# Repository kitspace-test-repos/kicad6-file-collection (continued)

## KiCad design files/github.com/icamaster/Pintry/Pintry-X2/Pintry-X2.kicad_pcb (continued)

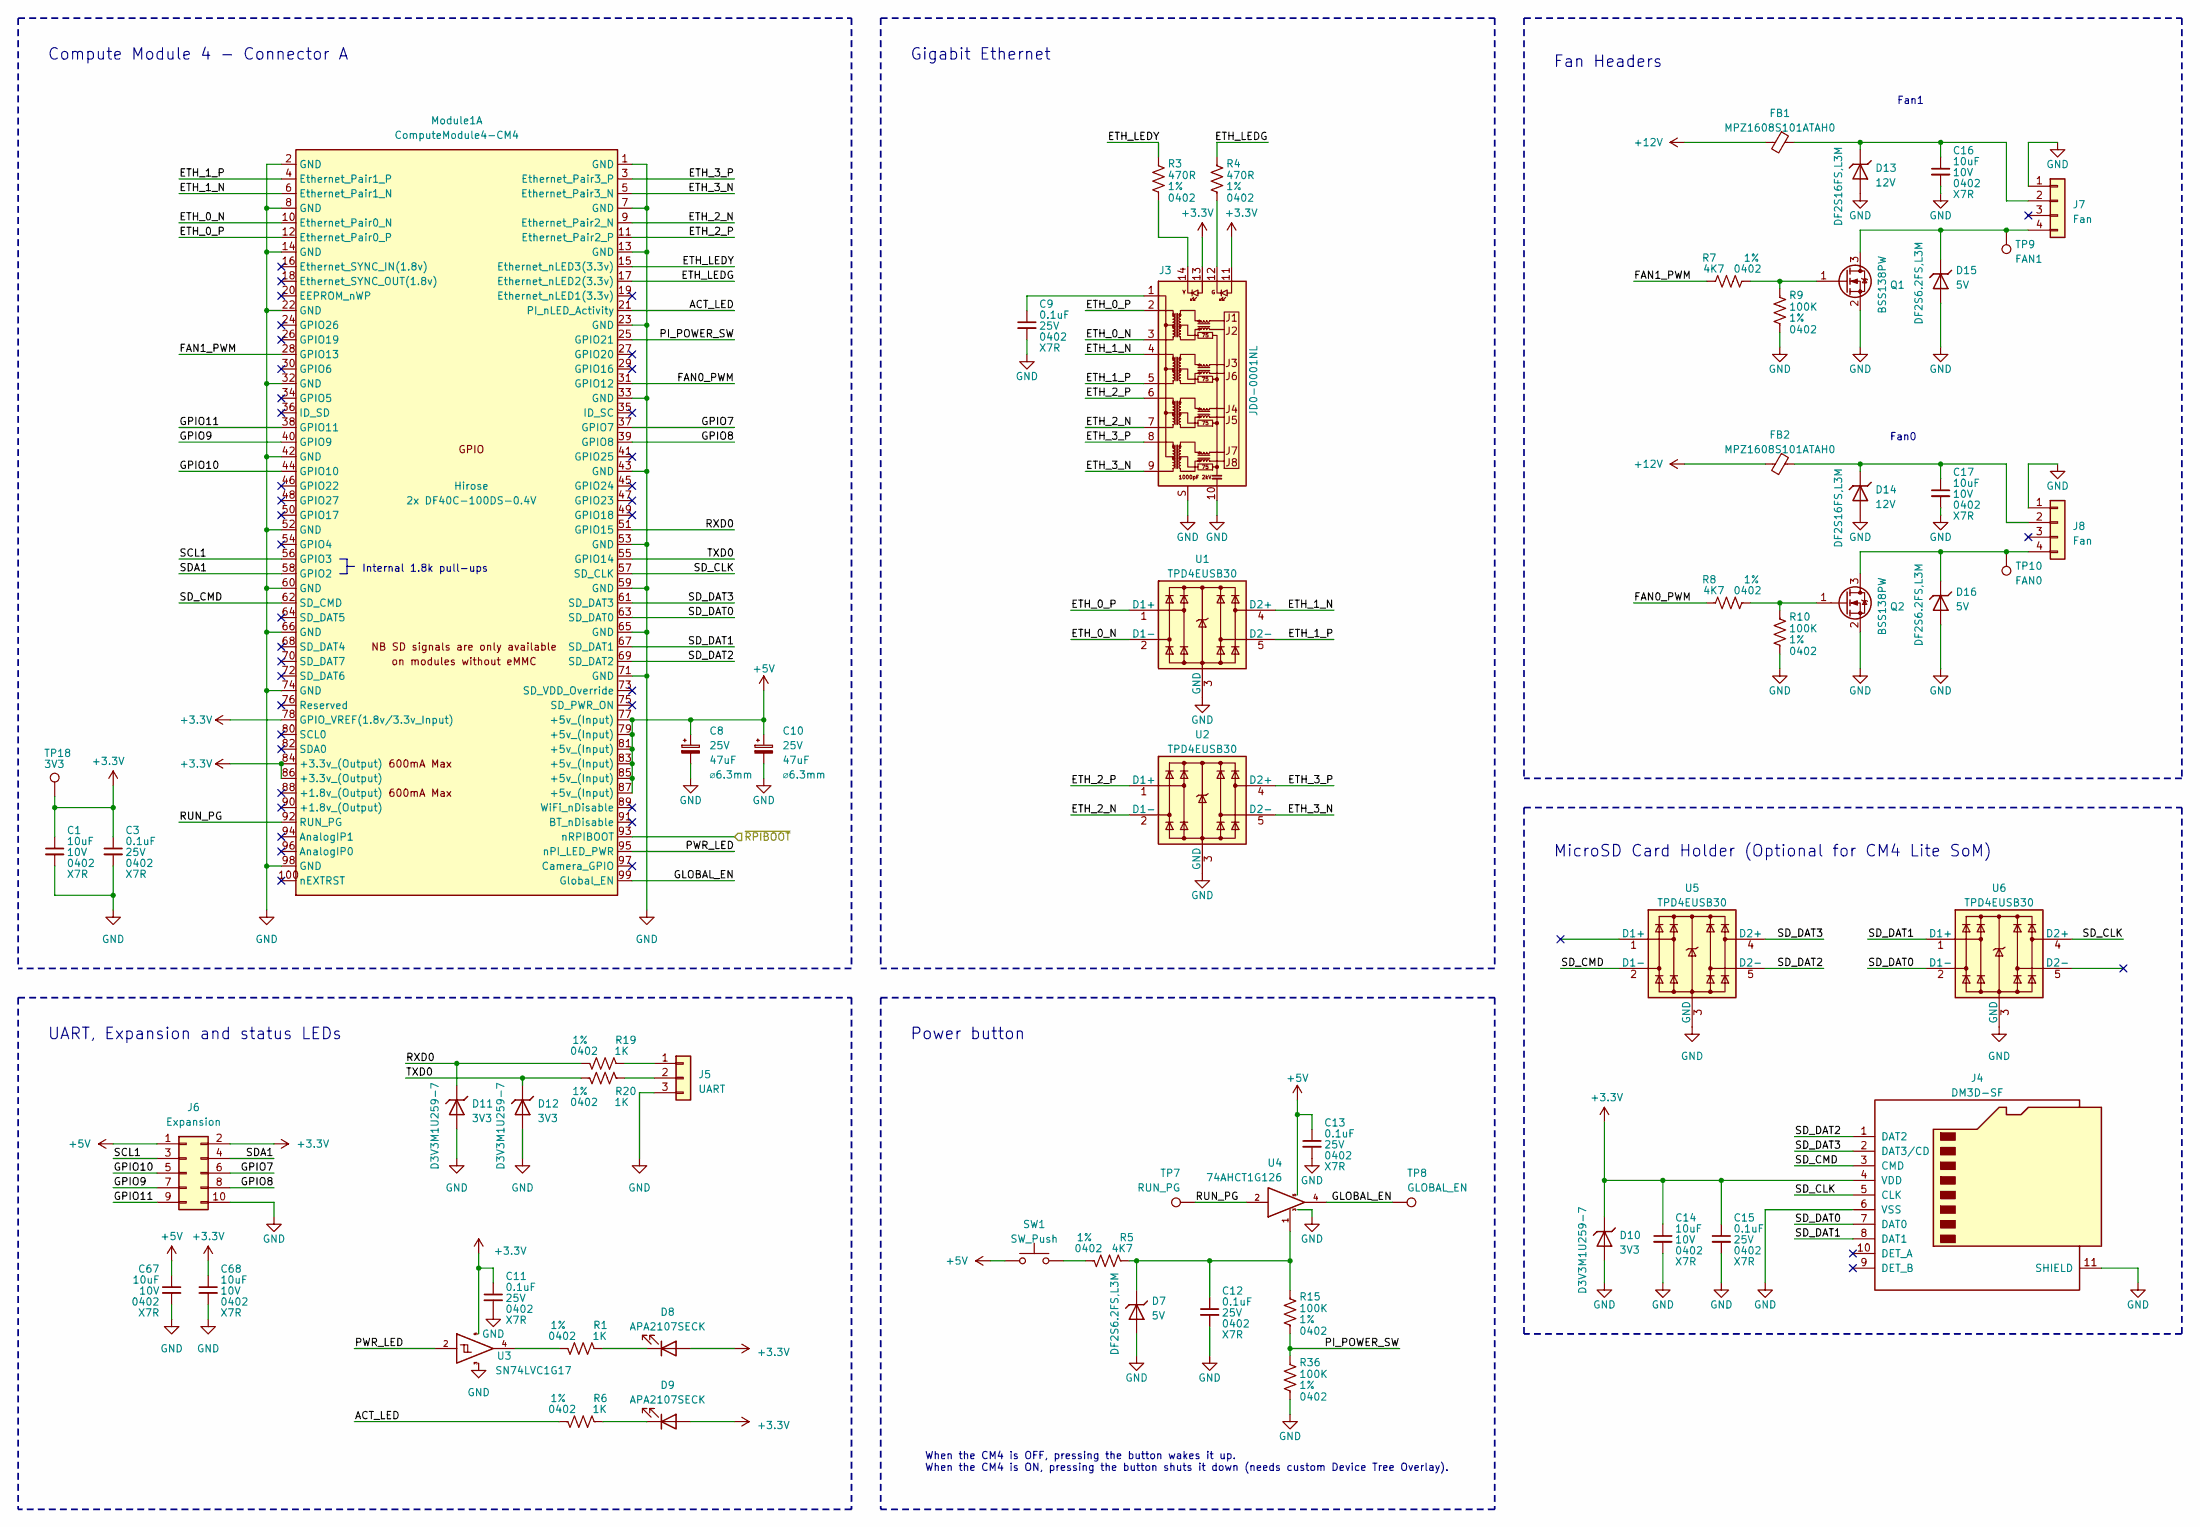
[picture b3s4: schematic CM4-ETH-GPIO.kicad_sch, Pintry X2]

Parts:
C1, C14, C16, C17, C67, C68: 10uF; C_0402_1005Metric; Voltage Rating 10V
C3, C9, C11, C12, C13, C15: 0.1uF; C_0402_1005Metric; Voltage Rating 25V
C8, C10: 865080443007; CP_Elec_6.3x5.4; Voltage 25V; Part Number 865080443007
D7, D15, D16: DF2S6.2FS,L3M; D_SOD-923; Part Number DF2S6.2FS,L3M
D8, D9: APA2107SECK; PartNumber APA2107SECK/J4-PRV
D10, D11, D12: D3V3M1U259-7; D_SOD-923; Part Number D3V3M1U2S9-7
D13, D14: DF2S16FS,L3M; D_SOD-923; Part Number DF2S16FS,L3M
FB1, FB2: MPZ1608S101ATAH0; L_0603_1608Metric; Part Number MPZ1608S101ATAH0
J3: JD0-0001NL; Pulse-JD0-0001NL-0-0-MFG; Part Number JD0-0001NL
J4: DM3D-SF; microSD_HC_Hirose_DM3D-SF; Part Number DM3D-SF
J5: UART; PinHeader_1x03_P2.54mm_Vertical; Part Number PH1-03-UA
J6: Expansion; PinHeader_2x05_P2.54mm_Vertical; Part Number 2PH2-10-UA
J7, J8: Fan; Molex_KK-254_AE-6410-04A_1x04_P2.54mm_Vertical; Part Number 47053-1000
Module1: ComputeModule4-CM4; Raspberry-Pi-4-Compute-Module; Part Number 2x DF40C-100DS-0.4V
Q1, Q2: BSS138PW; SOT-323_SC-70; Part Number BSS138PW,115
R1, R6, R19, R20: 1K; R_0402_1005Metric; Tolerance 1%
R3, R4: 470R; R_0402_1005Metric; Tolerance 1%
R5, R7, R8: 4K7; R_0402_1005Metric; Tolerance 1%
R9, R10, R15, R36: 100K; R_0402_1005Metric; Tolerance 1%
SW1: SW_Push; SW_Tactile_SPST_Angled_PTS645Vx58-2LFS; Part Number 1-1825027-4
TP7: RUN_PG; TestPoint_Pad_D1.0mm
TP8: GLOBAL_EN; TestPoint_Pad_D1.0mm
TP9: FAN1; TestPoint_Pad_D1.0mm
TP10: FAN0; TestPoint_Pad_D1.0mm
TP18: 3V3; TestPoint_Pad_D1.0mm
U1, U2, U5, U6: TPD4EUSB30; USON-10_2.5x1.0mm_P0.5mm; Part Number TPD4EUSB30DQAR
U3: SN74LVC1G17; SOT-23-5; Part Number SN74LVC1G17DBVR
U4: 74AHCT1G126; SOT-353_SC-70-5; Part Number 74AHCT1G126SE-7

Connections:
+3V3: C1.1, C3.1, C11.1, C14.1, C15.1, C68.1, D8.2 (A), D9.2 (A), D10.1 (K), J3.11, J3.13, J4.4 (VDD), J6.2, Module1.78 (GPIO_VREF(1.8v/3.3v_Input)), Module1.84 (+3.3v_(Output)), Module1.86 (+3.3v_(Output)), TP18.1, U3.5 (VCC); also elsewhere on the board
+5V: C8.1, C10.1, C13.1, C67.1, J6.1, Module1.77 (+5v_(Input)), Module1.79 (+5v_(Input)), Module1.81 (+5v_(Input)), Module1.83 (+5v_(Input)), Module1.85 (+5v_(Input)), Module1.87 (+5v_(Input)), SW1.1, U4.5 (VCC); also elsewhere on the board
+12V: FB1.2, FB2.2; also elsewhere on the board
/CM4-ETH-GPIO/ACT_LED: Module1.21 (PI_nLED_Activity), R6.2
/CM4-ETH-GPIO/ETH_0_N: J3.3, Module1.10 (Ethernet_Pair0_N), U1.2 (D1-), U1.9
/CM4-ETH-GPIO/ETH_0_P: J3.2, Module1.12 (Ethernet_Pair0_P), U1.1 (D1+), U1.10
/CM4-ETH-GPIO/ETH_1_N: J3.4, Module1.6 (Ethernet_Pair1_N), U1.4 (D2+), U1.7
/CM4-ETH-GPIO/ETH_1_P: J3.5, Module1.4 (Ethernet_Pair1_P), U1.5 (D2-), U1.6
/CM4-ETH-GPIO/ETH_2_N: J3.7, Module1.9 (Ethernet_Pair2_N), U2.2 (D1-), U2.9
/CM4-ETH-GPIO/ETH_2_P: J3.6, Module1.11 (Ethernet_Pair2_P), U2.1 (D1+), U2.10
/CM4-ETH-GPIO/ETH_3_N: J3.9, Module1.5 (Ethernet_Pair3_N), U2.5 (D2-), U2.6
/CM4-ETH-GPIO/ETH_3_P: J3.8, Module1.3 (Ethernet_Pair3_P), U2.4 (D2+), U2.7
/CM4-ETH-GPIO/ETH_LEDG: Module1.17 (Ethernet_nLED2(3.3v)), R4.1
/CM4-ETH-GPIO/ETH_LEDY: Module1.15 (Ethernet_nLED3(3.3v)), R3.1
/CM4-ETH-GPIO/FAN0_PWM: Module1.31 (GPIO12), R8.1
/CM4-ETH-GPIO/FAN1_PWM: Module1.28 (GPIO13), R7.1
/CM4-ETH-GPIO/GLOBAL_EN: Module1.99 (Global_EN), TP8.1, U4.4
/CM4-ETH-GPIO/GPIO7: J6.6, Module1.37 (GPIO7)
/CM4-ETH-GPIO/GPIO8: J6.8, Module1.39 (GPIO8)
/CM4-ETH-GPIO/GPIO9: J6.7, Module1.40 (GPIO9)
/CM4-ETH-GPIO/GPIO10: J6.5, Module1.44 (GPIO10)
/CM4-ETH-GPIO/GPIO11: J6.9, Module1.38 (GPIO11)
/CM4-ETH-GPIO/PI_POWER_SW: Module1.25 (GPIO21), R15.2, R36.1
/CM4-ETH-GPIO/PWR_LED: Module1.95 (nPI_LED_PWR), U3.2
/CM4-ETH-GPIO/RUN_PG: Module1.92 (RUN_PG), TP7.1, U4.2
/CM4-ETH-GPIO/RXD0: D11.1 (K), Module1.51 (GPIO15), R19.2
/CM4-ETH-GPIO/SCL1: J6.3, Module1.56 (GPIO3)
/CM4-ETH-GPIO/SDA1: J6.4, Module1.58 (GPIO2)
/CM4-ETH-GPIO/SD_CLK: J4.5 (CLK), Module1.57 (SD_CLK), U6.4 (D2+), U6.7
/CM4-ETH-GPIO/SD_CMD: J4.3 (CMD), Module1.62 (SD_CMD), U5.2 (D1-), U5.9
/CM4-ETH-GPIO/SD_DAT0: J4.7 (DAT0), Module1.63 (SD_DAT0), U6.2 (D1-), U6.9
/CM4-ETH-GPIO/SD_DAT1: J4.8 (DAT1), Module1.67 (SD_DAT1), U6.1 (D1+), U6.10
/CM4-ETH-GPIO/SD_DAT2: J4.1 (DAT2), Module1.69 (SD_DAT2), U5.5 (D2-), U5.6
/CM4-ETH-GPIO/SD_DAT3: J4.2 (DAT3/CD), Module1.61 (SD_DAT3), U5.4 (D2+), U5.7
/CM4-ETH-GPIO/TXD0: D12.1 (K), Module1.55 (GPIO14), R20.2
/CM4-ETH-GPIO/~RPIBOOT: Module1.93 (nRPIBOOT); also elsewhere on the board
GND: C1.2, C3.2, C8.2, C9.2, C10.2, C11.2, C12.2, C13.2, C14.2, C15.2, C16.2, C17.2, C67.2, C68.2, D7.2 (A), D10.2 (A), D11.2 (A), D12.2 (A), D13.2 (A), D14.2 (A), D15.2 (A), D16.2 (A), J3.10, J3.S, J4.6 (VSS), J4.11 (SHIELD), J5.3, J6.10, J7.1, J8.1, Module1.1 (GND), Module1.2 (GND), Module1.7 (GND), Module1.8 (GND), Module1.13 (GND), Module1.14 (GND), Module1.22 (GND), Module1.23 (GND), Module1.32 (GND), Module1.33 (GND), Module1.42 (GND), Module1.43 (GND), Module1.52 (GND), Module1.53 (GND), Module1.59 (GND), Module1.60 (GND), Module1.65 (GND), Module1.66 (GND), Module1.71 (GND), Module1.74 (GND), Module1.98 (GND), Q1.2 (S), Q2.2 (S), R9.2, R10.2, R36.2, U1.3 (GND), U1.8 (GND), U2.3 (GND), U2.8 (GND), U3.3 (GND), U4.3 (GND), U5.3 (GND), U5.8 (GND), U6.3 (GND), U6.8 (GND); also elsewhere on the board
unnamed: C9.1, J3.1
unnamed: C12.1, D7.1 (K), R5.1, R15.1, U4.1
unnamed: C16.1, D13.1 (K), FB1.1, J7.2
unnamed: C17.1, D14.1 (K), FB2.1, J8.2
unnamed: D8.1 (K), R1.1
unnamed: D9.1 (K), R6.1
unnamed: D15.1 (K), J7.4, Q1.3 (D), TP9.1
unnamed: D16.1 (K), J8.4, Q2.3 (D), TP10.1
unnamed: J3.12, R4.2
unnamed: J3.14, R3.2
unnamed: J5.1, R19.1
unnamed: J5.2, R20.1
unnamed: Q1.1 (G), R7.2, R9.1
unnamed: Q2.1 (G), R8.2, R10.1
unnamed: R1.2, U3.4
unnamed: R5.2, SW1.2

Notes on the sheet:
Gigabit Ethernet
Internal 1.8k pull-ups
When the CM4 is OFF, pressing the button wakes it up. When the CM4 is ON, pressing the button shuts it down (needs custom Device Tree Overlay).
UART, Expansion and status LEDs
MicroSD Card Holder (Optional for CM4 Lite SoM)
Fan1
Fan0
Fan Headers
Power button
Compute Module 4 - Connector A

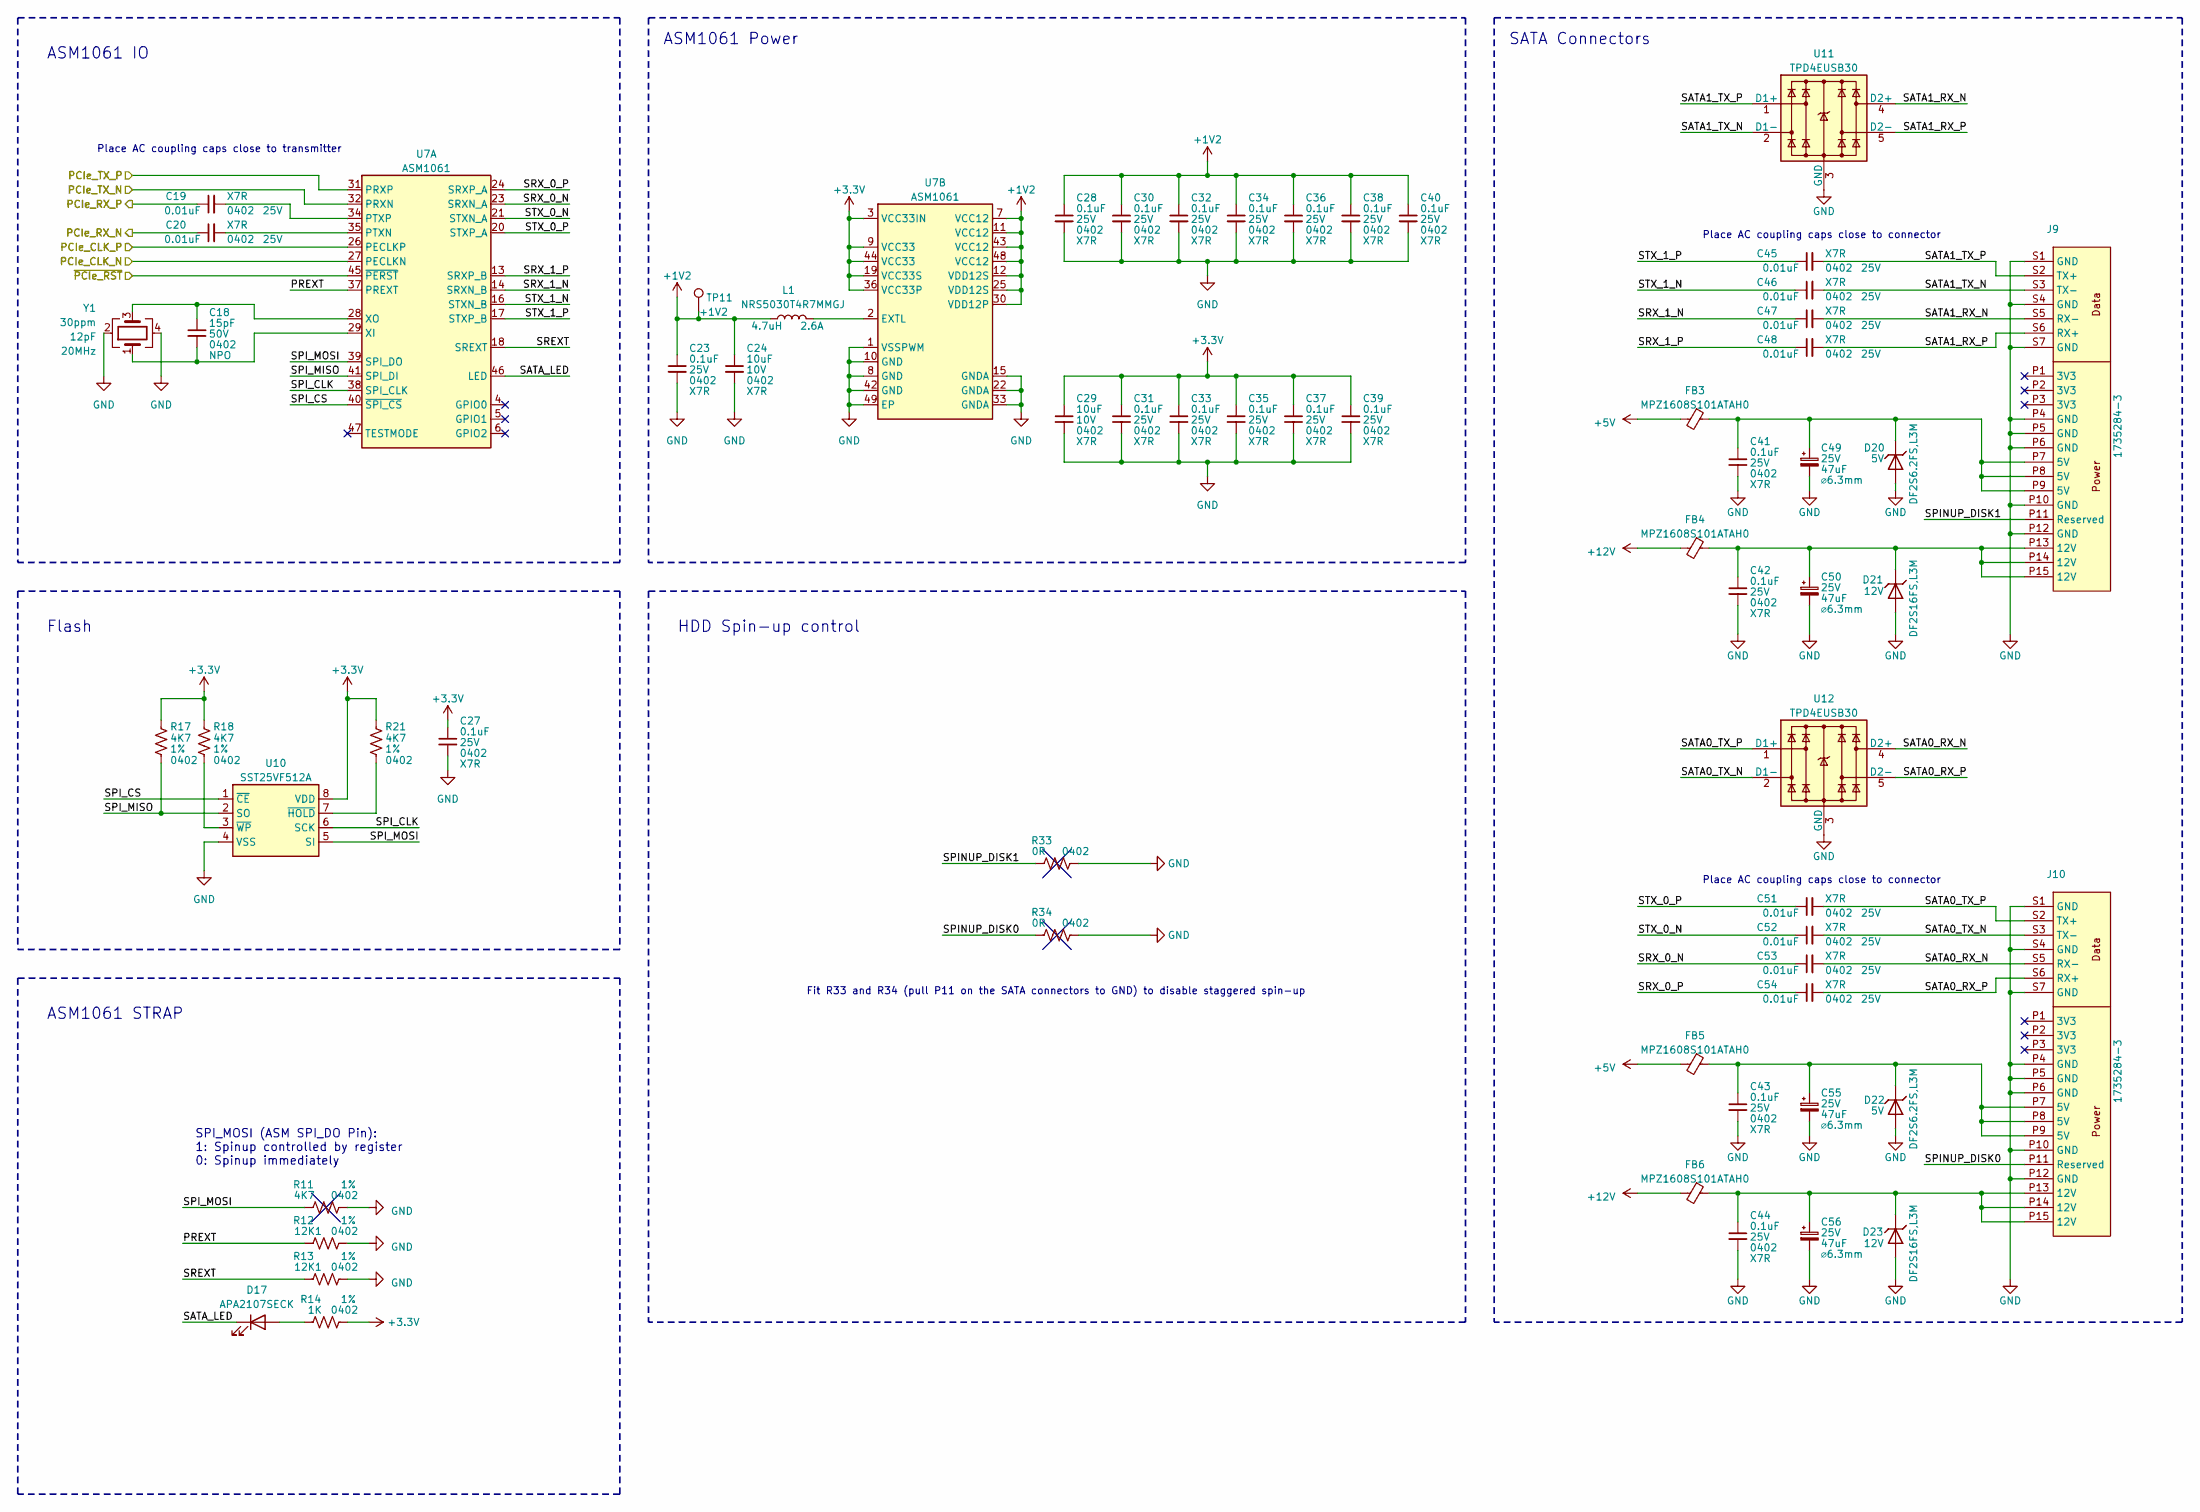
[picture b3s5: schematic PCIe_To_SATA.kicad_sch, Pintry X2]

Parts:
C18: 15pF; C_0402_1005Metric; Voltage Rating 50V
C19, C20, C45, C46, C47, C48, C51, C52, C53, C54: 0.01uF; C_0402_1005Metric; Voltage Rating 25V
C23, C27, C28, C30, C31, C32, C33, C34, C35, C36, C37, C38, C39, C40, C41, C42, C43, C44: 0.1uF; C_0402_1005Metric; Voltage Rating 25V
C24, C29: 10uF; C_0402_1005Metric; Voltage Rating 10V
C49, C50, C55, C56: 865080443007; CP_Elec_6.3x5.4; Voltage 25V; Part Number 865080443007
D17: APA2107SECK; PartNumber APA2107SECK/J4-PRV
D20, D22: DF2S6.2FS,L3M; D_SOD-923; Part Number DF2S6.2FS,L3M
D21, D23: DF2S16FS,L3M; D_SOD-923; Part Number DF2S16FS,L3M
FB3, FB4, FB5, FB6: MPZ1608S101ATAH0; L_0603_1608Metric; Part Number MPZ1608S101ATAH0
J9, J10: 1735284-3; TE_1735284-3; Part Number 1735284-3
L1: NRS5030T4R7MMGJ; L_Taiyo-Yuden_NR-50xx; Current Rating 2.6A; Part Number NRS5030T4R7MMGJ
R11, R17, R18, R21: 4K7; R_0402_1005Metric; Tolerance 1%
R12, R13: 12K1; R_0402_1005Metric; Tolerance 1%
R14: 1K; R_0402_1005Metric; Tolerance 1%
R33, R34: 0R; R_0402_1005Metric; Tolerance 1%
TP11: +1V2; TestPoint_Pad_D1.0mm
U7: ASM1061; QFN-48-1EP_7x7mm_P0.5mm_EP4.025x4.025mm
U10: SST25VF512A; SOIC-8_3.9x4.9mm_P1.27mm; Part Number SST25VF512A-33-4I-SAE-T
U11, U12: TPD4EUSB30; USON-10_2.5x1.0mm_P0.5mm; Part Number TPD4EUSB30DQAR
Y1: ECS-200-12-33-AGN-TR; Crystal_SMD_3225-4Pin_3.2x2.5mm; Part Number ECS-200-12-33-AGN-TR

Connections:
+1V2: C23.1, C24.1, C28.1, C30.1, C32.1, C34.1, C36.1, C38.1, C40.1, L1.1, TP11.1, U7.7 (VCC12), U7.11 (VCC12), U7.12 (VDD12S), U7.25 (VDD12S), U7.30 (VDD12P), U7.43 (VCC12), U7.48 (VCC12)
+3V3: C27.1, C29.1, C31.1, C33.1, C35.1, C37.1, C39.1, R14.2, R17.1, R18.1, R21.1, U7.3 (VCC33IN), U7.9 (VCC33), U7.19 (VCC33S), U7.36 (VCC33P), U7.44 (VCC33), U10.8 (VDD); also elsewhere on the board
+5V: FB3.2, FB5.2; also elsewhere on the board
+12V: FB4.2, FB6.2; also elsewhere on the board
/CM4-USB-PCIe/PCIe_CLK_N: U7.27 (PECLKN); also elsewhere on the board
/CM4-USB-PCIe/PCIe_CLK_P: U7.26 (PECLKP); also elsewhere on the board
/CM4-USB-PCIe/PCIe_RX_N: C20.1; also elsewhere on the board
/CM4-USB-PCIe/PCIe_RX_P: C19.1; also elsewhere on the board
/CM4-USB-PCIe/PCIe_TX_N: U7.32 (PRXN); also elsewhere on the board
/CM4-USB-PCIe/PCIe_TX_P: U7.31 (PRXP); also elsewhere on the board
/CM4-USB-PCIe/~PCIe_RST: U7.45 (~PERST); also elsewhere on the board
/PCIe to SATA/PREXT: R12.1, U7.37 (PREXT)
/PCIe to SATA/SATA0_RX_N: C53.2, J10.S5 (RX-), U12.4 (D2+), U12.7
/PCIe to SATA/SATA0_RX_P: C54.2, J10.S6 (RX+), U12.5 (D2-), U12.6
/PCIe to SATA/SATA0_TX_N: C52.2, J10.S3 (TX-), U12.2 (D1-), U12.9
/PCIe to SATA/SATA0_TX_P: C51.2, J10.S2 (TX+), U12.1 (D1+), U12.10
/PCIe to SATA/SATA1_RX_N: C47.2, J9.S5 (RX-), U11.4 (D2+), U11.7
/PCIe to SATA/SATA1_RX_P: C48.2, J9.S6 (RX+), U11.5 (D2-), U11.6
/PCIe to SATA/SATA1_TX_N: C46.2, J9.S3 (TX-), U11.2 (D1-), U11.9
/PCIe to SATA/SATA1_TX_P: C45.2, J9.S2 (TX+), U11.1 (D1+), U11.10
/PCIe to SATA/SATA_LED: D17.1 (K), U7.46 (LED)
/PCIe to SATA/SPINUP_DISK0: J10.P11 (Reserved), R34.1
/PCIe to SATA/SPINUP_DISK1: J9.P11 (Reserved), R33.1
/PCIe to SATA/SPI_CLK: U7.38 (SPI_CLK), U10.6 (SCK)
/PCIe to SATA/SPI_CS: U7.40 (~SPI_CS), U10.1 (~CE)
/PCIe to SATA/SPI_MISO: R17.2, U7.41 (SPI_DI), U10.2 (SO)
/PCIe to SATA/SPI_MOSI: R11.1, U7.39 (SPI_DO), U10.5 (SI)
/PCIe to SATA/SREXT: R13.1, U7.18 (SREXT)
/PCIe to SATA/SRX_0_N: C53.1, U7.23 (SRXN_A)
/PCIe to SATA/SRX_0_P: C54.1, U7.24 (SRXP_A)
/PCIe to SATA/SRX_1_N: C47.1, U7.14 (SRXN_B)
/PCIe to SATA/SRX_1_P: C48.1, U7.13 (SRXP_B)
/PCIe to SATA/STX_0_N: C52.1, U7.21 (STXN_A)
/PCIe to SATA/STX_0_P: C51.1, U7.20 (STXP_A)
/PCIe to SATA/STX_1_N: C46.1, U7.16 (STXN_B)
/PCIe to SATA/STX_1_P: C45.1, U7.17 (STXP_B)
GND: C23.2, C24.2, C27.2, C28.2, C29.2, C30.2, C31.2, C32.2, C33.2, C34.2, C35.2, C36.2, C37.2, C38.2, C39.2, C40.2, C41.2, C42.2, C43.2, C44.2, C49.2, C50.2, C55.2, C56.2, D20.2 (A), D21.2 (A), D22.2 (A), D23.2 (A), J9.P4 (GND), J9.P5 (GND), J9.P6 (GND), J9.P10 (GND), J9.P12 (GND), J9.S1 (GND), J9.S4 (GND), J9.S7 (GND), J10.P4 (GND), J10.P5 (GND), J10.P6 (GND), J10.P10 (GND), J10.P12 (GND), J10.S1 (GND), J10.S4 (GND), J10.S7 (GND), R11.2, R12.2, R13.2, R33.2, R34.2, U7.1 (VSSPWM), U7.8 (GND), U7.10 (GND), U7.15 (GNDA), U7.22 (GNDA), U7.33 (GNDA), U7.42 (GND), U7.49 (EP), U10.4 (VSS), U11.3 (GND), U11.8 (GND), U12.3 (GND), U12.8 (GND), Y1.2, Y1.4; also elsewhere on the board
unnamed: C18.1, U7.28 (XO), Y1.3
unnamed: C18.2, U7.29 (XI), Y1.1
unnamed: C19.2, U7.34 (PTXP)
unnamed: C20.2, U7.35 (PTXN)
unnamed: C41.1, C49.1, D20.1 (K), FB3.1, J9.P7 (5V), J9.P8 (5V), J9.P9 (5V)
unnamed: C42.1, C50.1, D21.1 (K), FB4.1, J9.P13 (12V), J9.P14 (12V), J9.P15 (12V)
unnamed: C43.1, C55.1, D22.1 (K), FB5.1, J10.P7 (5V), J10.P8 (5V), J10.P9 (5V)
unnamed: C44.1, C56.1, D23.1 (K), FB6.1, J10.P13 (12V), J10.P14 (12V), J10.P15 (12V)
unnamed: D17.2 (A), R14.1
unnamed: L1.2, U7.2 (EXTL)
unnamed: R18.2, U10.3 (~WP)
unnamed: R21.2, U10.7 (~HOLD)

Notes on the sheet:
SATA Connectors
ASM1061 STRAP
ASM1061 IO
Flash
Place AC coupling caps close to transmitter
SPI_MOSI (ASM SPI_DO Pin): 1: Spinup controlled by register 0: Spinup immediately
HDD Spin-up control
Place AC coupling caps close to connector
Fit R33 and R34 (pull P11 on the SATA connectors to GND) to disable staggered spin-up
ASM1061 Power

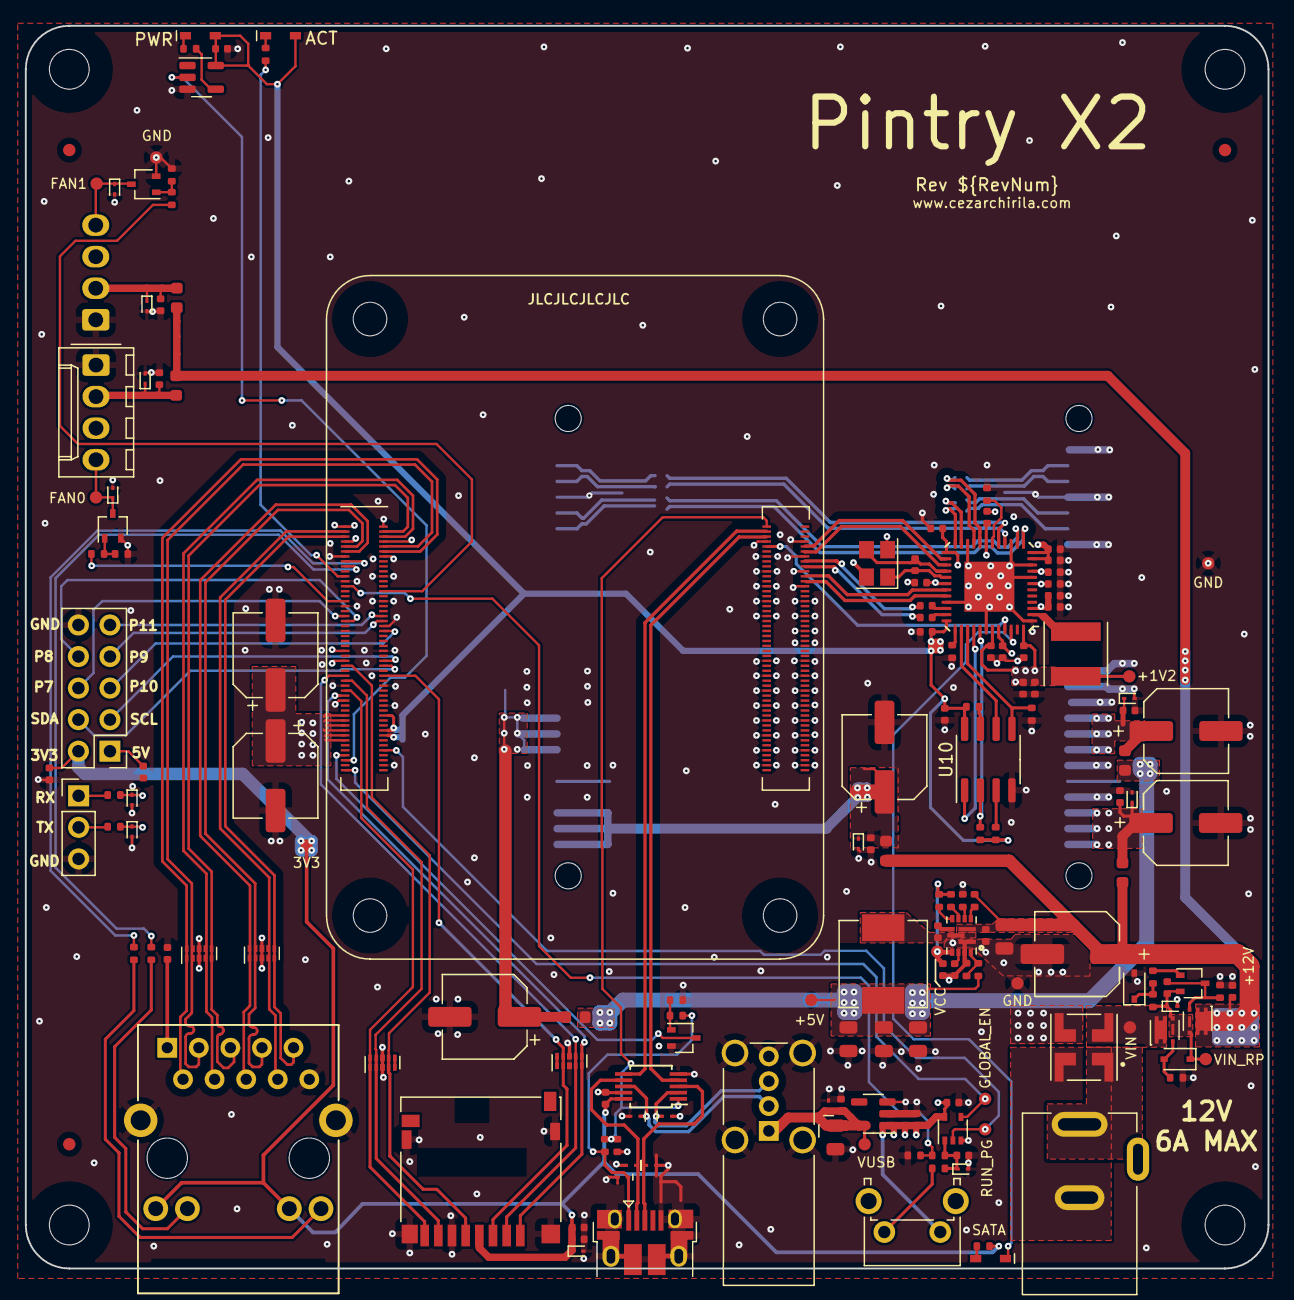
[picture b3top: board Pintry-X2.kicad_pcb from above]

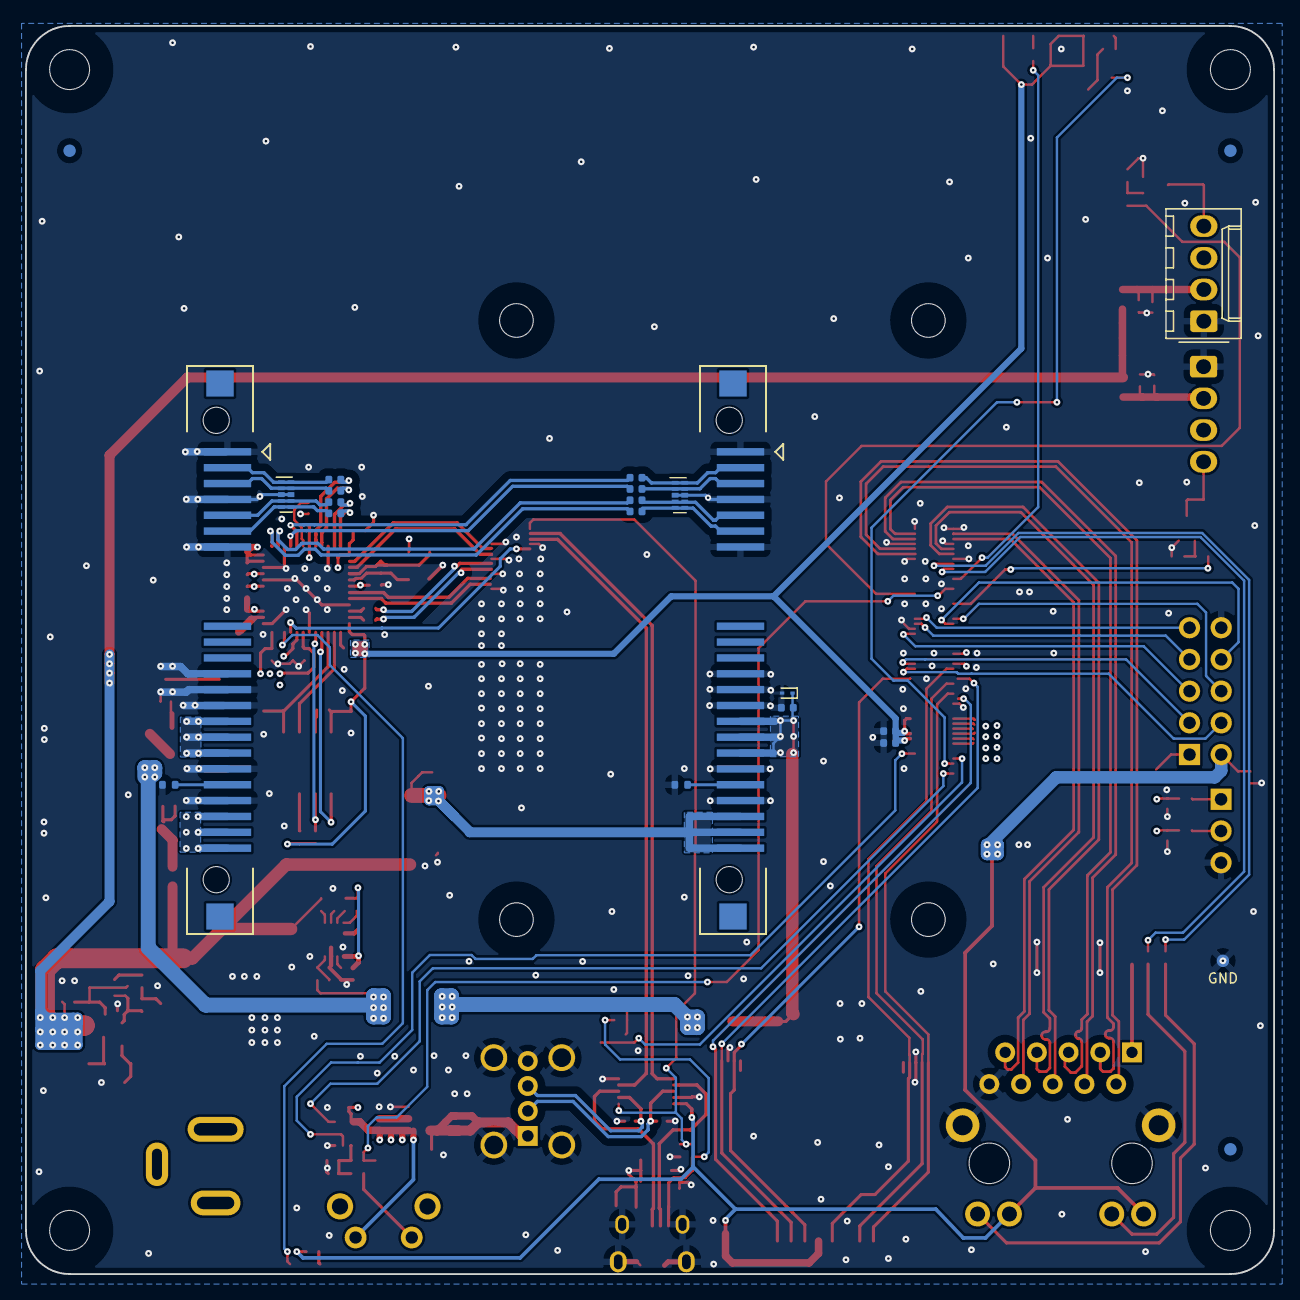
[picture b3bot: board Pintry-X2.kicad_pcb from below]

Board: 4 copper layers, 100.0 x 100.0 mm, 193 parts (23 on the bottom side), 125 nets.

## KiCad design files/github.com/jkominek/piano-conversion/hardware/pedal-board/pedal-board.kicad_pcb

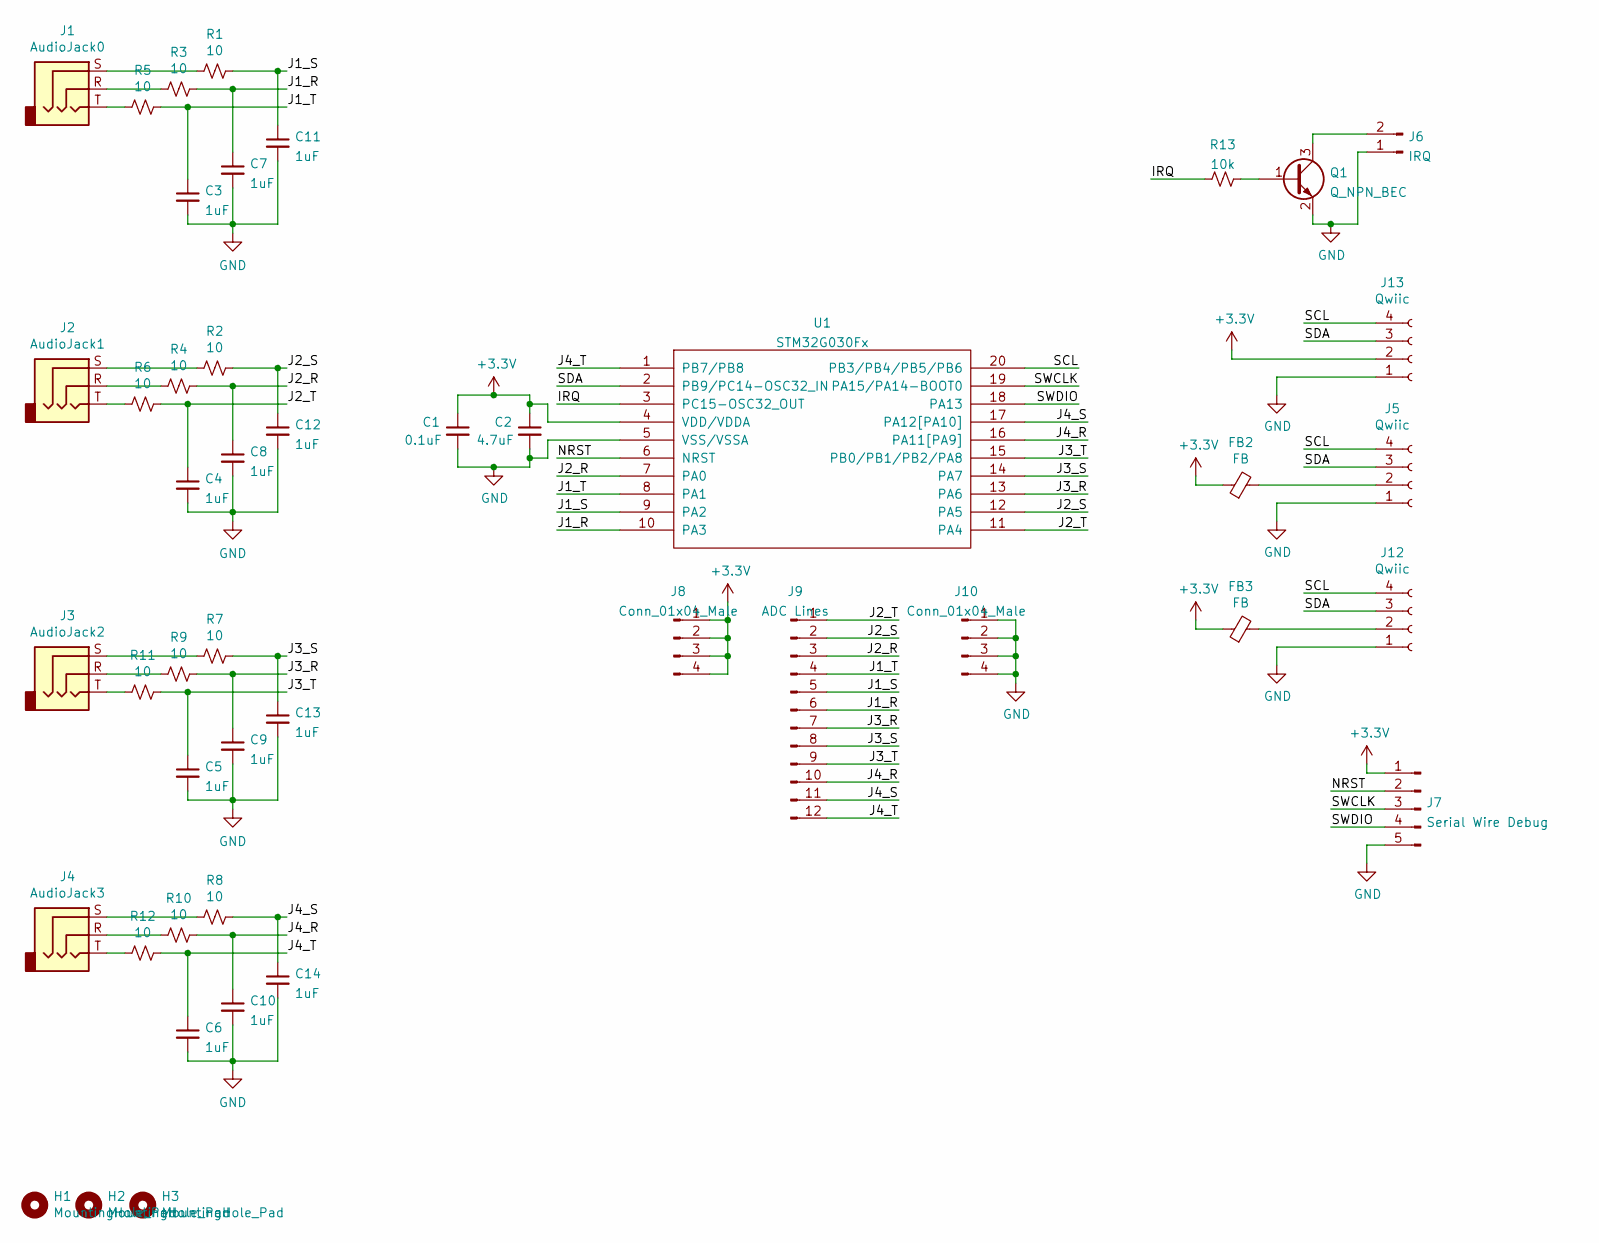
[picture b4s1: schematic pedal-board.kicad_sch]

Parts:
C1: 0.1uF; C_0805_2012Metric_Pad1.18x1.45mm_HandSolder
C2: 4.7uF; C_0805_2012Metric_Pad1.18x1.45mm_HandSolder
C3, C4, C5, C6, C7, C8, C9, C10, C11, C12, C13, C14: 1uF; C_0805_2012Metric_Pad1.18x1.45mm_HandSolder
FB2, FB3: FB; L_0805_2012Metric_Pad1.05x1.20mm_HandSolder
H1, H2, H3: MountingHole_Pad; MountingHole_3.2mm_M3
J1: AudioJack0; SJ-63053A
J2: AudioJack1; SJ-63053A
J3: AudioJack2; SJ-63053A
J4: AudioJack3; SJ-63053A
J5, J12: Qwiic; JST_SH_SM04B-SRSS-TB_04x1.00mm_Angled
J6: IRQ; PinHeader_1x02_P2.54mm_Vertical
J7: Serial Wire Debug; PinHeader_1x05_P2.54mm_Vertical
J8, J10: Conn_01x04_Male; PinHeader_1x04_P2.54mm_Vertical
J9: ADC Lines; PinHeader_1x12_P2.54mm_Vertical
J13: Qwiic; PinHeader_1x04_P2.54mm_Vertical
Q1: Q_NPN_BEC; SOT-23
R1, R2, R3, R4, R5, R6, R7, R8, R9, R10, R11, R12: 10; R_0805_2012Metric_Pad1.20x1.40mm_HandSolder
R13: 10k; R_0805_2012Metric_Pad1.20x1.40mm_HandSolder
U1: STM32G030Fx; TSSOP-20_4.4x6.5mm_P0.65mm

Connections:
+3V3: C1.1, C2.1, FB2.1, FB3.1, J7.1, J8.1, J8.2, J8.3, J8.4, J13.2, U1.4 (VDD/VDDA)
/IRQ: R13.1, U1.3 (PC15-OSC32_OUT)
/J1_R: C7.1, J9.6, R3.1, U1.10 (PA3)
/J1_S: C11.1, J9.5, R1.1, U1.9 (PA2)
/J1_T: C3.1, J9.4, R5.1, U1.8 (PA1)
/J2_R: C8.1, J9.3, R4.1, U1.7 (PA0)
/J2_S: C12.1, J9.2, R2.1, U1.12 (PA5)
/J2_T: C4.1, J9.1, R6.1, U1.11 (PA4)
/J3_R: C9.1, J9.7, R9.1, U1.13 (PA6)
/J3_S: C13.1, J9.8, R7.1, U1.14 (PA7)
/J3_T: C5.1, J9.9, R11.1, U1.15 (PB0/PB1/PB2/PA8)
/J4_R: C10.1, J9.10, R10.1, U1.16 (PA11[PA9])
/J4_S: C14.1, J9.11, R8.1, U1.17 (PA12[PA10])
/J4_T: C6.1, J9.12, R12.1, U1.1 (PB7/PB8)
/NRST: J7.2, U1.6 (NRST)
/SCL: J5.4, J12.4, J13.4, U1.20 (PB3/PB4/PB5/PB6)
/SDA: J5.3, J12.3, J13.3, U1.2 (PB9/PC14-OSC32_IN)
/SWCLK: J7.3, U1.19 (PA15/PA14-BOOT0)
/SWDIO: J7.4, U1.18 (PA13)
GND: C1.2, C2.2, C3.2, C4.2, C5.2, C6.2, C7.2, C8.2, C9.2, C10.2, C11.2, C12.2, C13.2, C14.2, J5.1, J6.1, J7.5, J10.1, J10.2, J10.3, J10.4, J12.1, J13.1, Q1.2 (E), U1.5 (VSS/VSSA)
unnamed: FB2.2, J5.2
unnamed: FB3.2, J12.2
unnamed: J1.R, R3.2
unnamed: J1.S, R1.2
unnamed: J1.T, R5.2
unnamed: J2.R, R4.2
unnamed: J2.S, R2.2
unnamed: J2.T, R6.2
unnamed: J3.R, R9.2
unnamed: J3.S, R7.2
unnamed: J3.T, R11.2
unnamed: J4.R, R10.2
unnamed: J4.S, R8.2
unnamed: J4.T, R12.2
unnamed: J6.2, Q1.3 (C)
unnamed: Q1.1 (B), R13.2

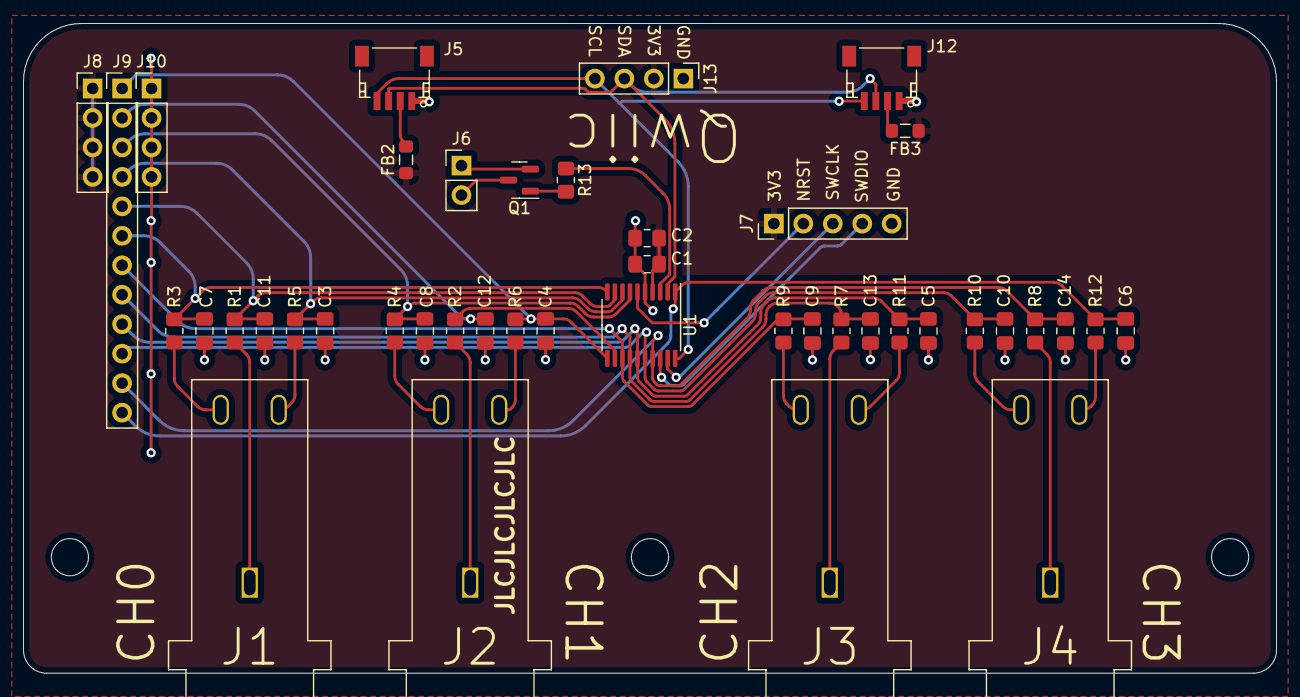
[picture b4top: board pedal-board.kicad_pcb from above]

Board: 2 copper layers, 108.0 x 56.0 mm, 46 parts (0 on the bottom side), 36 nets.

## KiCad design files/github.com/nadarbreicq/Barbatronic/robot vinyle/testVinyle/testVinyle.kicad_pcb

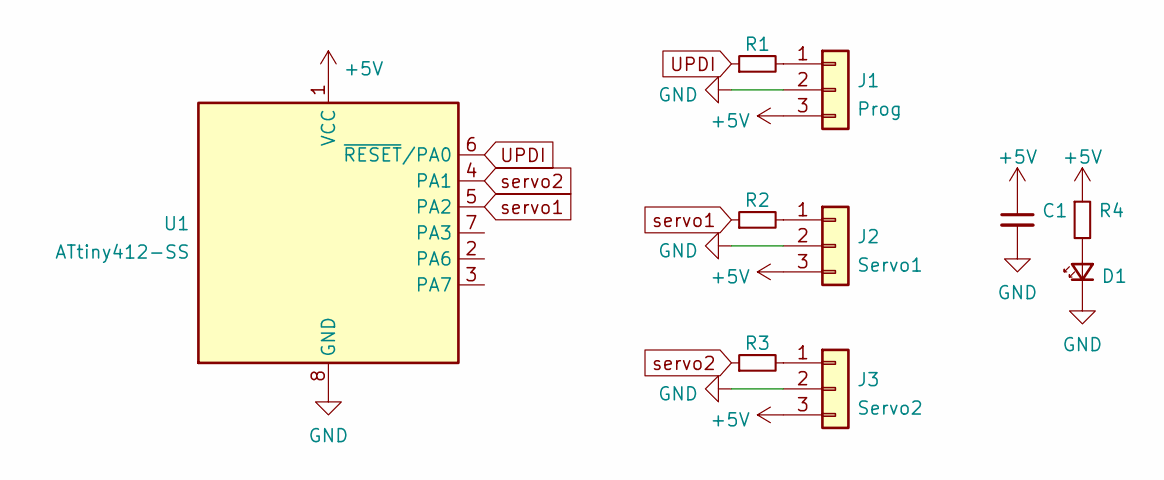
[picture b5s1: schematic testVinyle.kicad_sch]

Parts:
C1: C_Small; C_1206_3216Metric_Pad1.33x1.80mm_HandSolder
D1: LED_Small; LED_1210_3225Metric_Pad1.42x2.65mm_HandSolder
J1: Prog; PinHeader_1x03_22.54mm_Horizontal_SMD_Line
J2: Servo1; PinHeader_1x03_22.54mm_Horizontal_SMD_Line
J3: Servo2; PinHeader_1x03_22.54mm_Horizontal_SMD_Line
R1, R2, R3, R4: R_Small; R_1206_3216Metric_Pad1.30x1.75mm_HandSolder
U1: ATtiny412-SS; SOIC-8_3.9x4.9mm_P1.27mm

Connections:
+5V: C1.1, J1.3, J2.3, J3.3, R4.1, U1.1 (VCC)
GND: C1.2, D1.1 (K), J1.2, J2.2, J3.2, U1.8 (GND)
unnamed: D1.2 (A), R4.2
unnamed: J1.1, R1.2
unnamed: J2.1, R2.2
unnamed: J3.1, R3.2
UPDI: R1.1, U1.6 (~RESET/PA0)
servo1: R2.1, U1.5 (PA2)
servo2: R3.1, U1.4 (PA1)

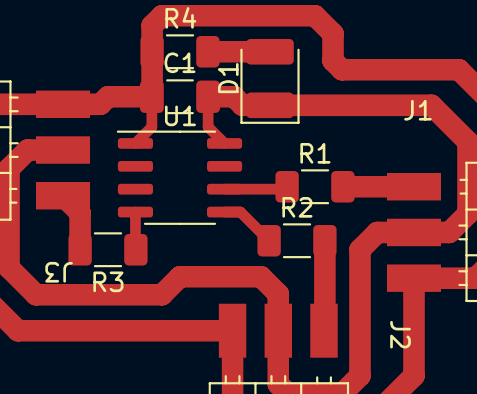
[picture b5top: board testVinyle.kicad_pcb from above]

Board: 2 copper layers, 10 parts (0 on the bottom side), 9 nets.
